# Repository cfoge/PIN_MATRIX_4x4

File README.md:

# PIN_MATRIX_4x4
Design for a 4x4 diy pin matrix

Make two, turn one at 90' to the other and join with a bolt, using a nut as a spacer between the two boards.
Now you can use 2mm banana plugs as patch pins, I push these bannnanas into M3 spacers with a bit of Nylock to make a nice little pin.

Tested and working.

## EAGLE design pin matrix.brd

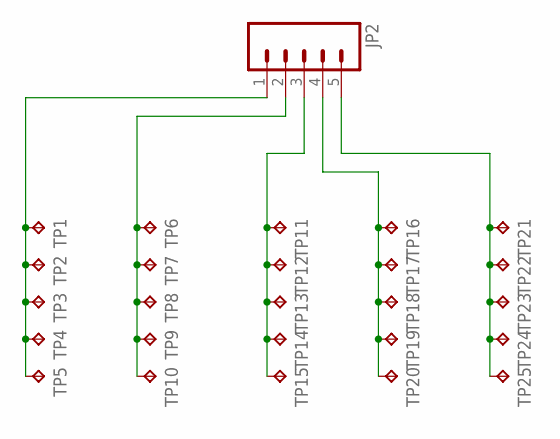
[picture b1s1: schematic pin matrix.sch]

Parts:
JP2: M05PTH; 1X05
TP1, TP2, TP3, TP4, TP5, TP6, TP7, TP8, TP9, TP10, TP11, TP12, TP13, TP14, TP15, TP16, TP17, TP18, TP19, TP20, TP21, TP22, TP23, TP24, TP25: TPPAD1-20; P1-20

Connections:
unnamed: JP2.1, TP1.TP, TP2.TP, TP3.TP, TP4.TP, TP5.TP
unnamed: JP2.2, TP6.TP, TP7.TP, TP8.TP, TP9.TP, TP10.TP
unnamed: JP2.3, TP11.TP, TP12.TP, TP13.TP, TP14.TP, TP15.TP
unnamed: JP2.5, TP21.TP, TP22.TP, TP23.TP, TP24.TP, TP25.TP
unnamed: JP2.4, TP16.TP, TP17.TP, TP18.TP, TP19.TP, TP20.TP

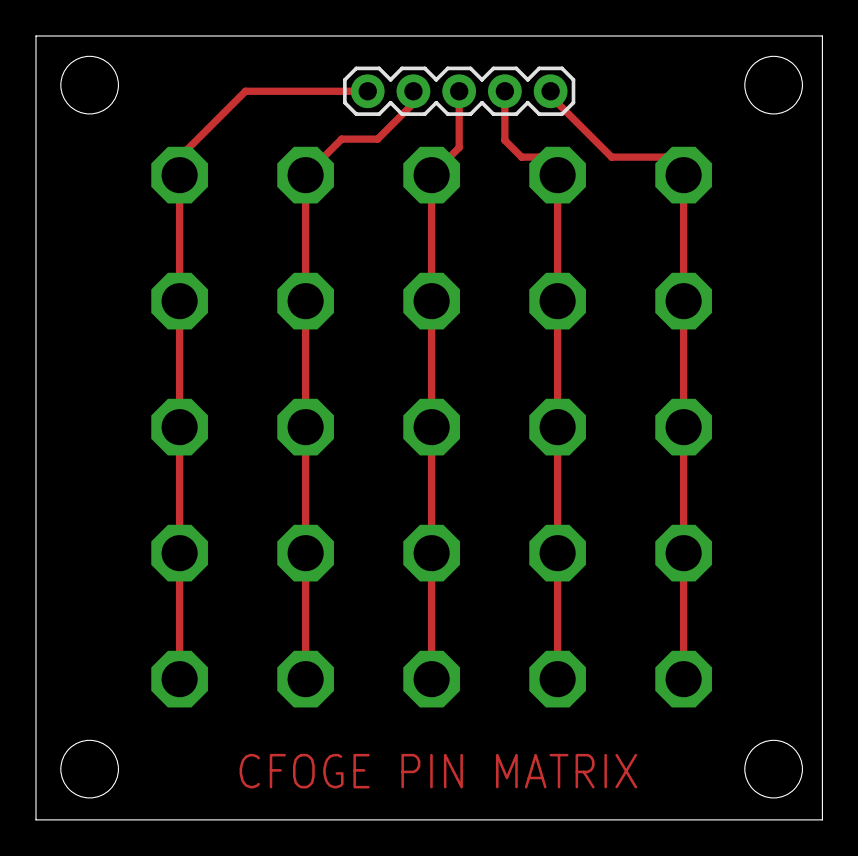
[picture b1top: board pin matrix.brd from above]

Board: 2 copper layers, 43.7 x 43.6 mm, 26 parts (0 on the bottom side), 5 nets.

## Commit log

2021-08-30 Add files via upload
    files for pin matrix
2021-09-09 images

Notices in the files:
parts and their libraries:
SparkFun-Connectors: Licensing: Creative Commons ShareAlike 4.0 International - https://creativecommons.org/licenses/by-sa/4.0
